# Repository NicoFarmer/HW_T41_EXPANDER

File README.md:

# HW_T41-EXPANDER
Carte électronique Electrobot basée sur un Teensy 4.1

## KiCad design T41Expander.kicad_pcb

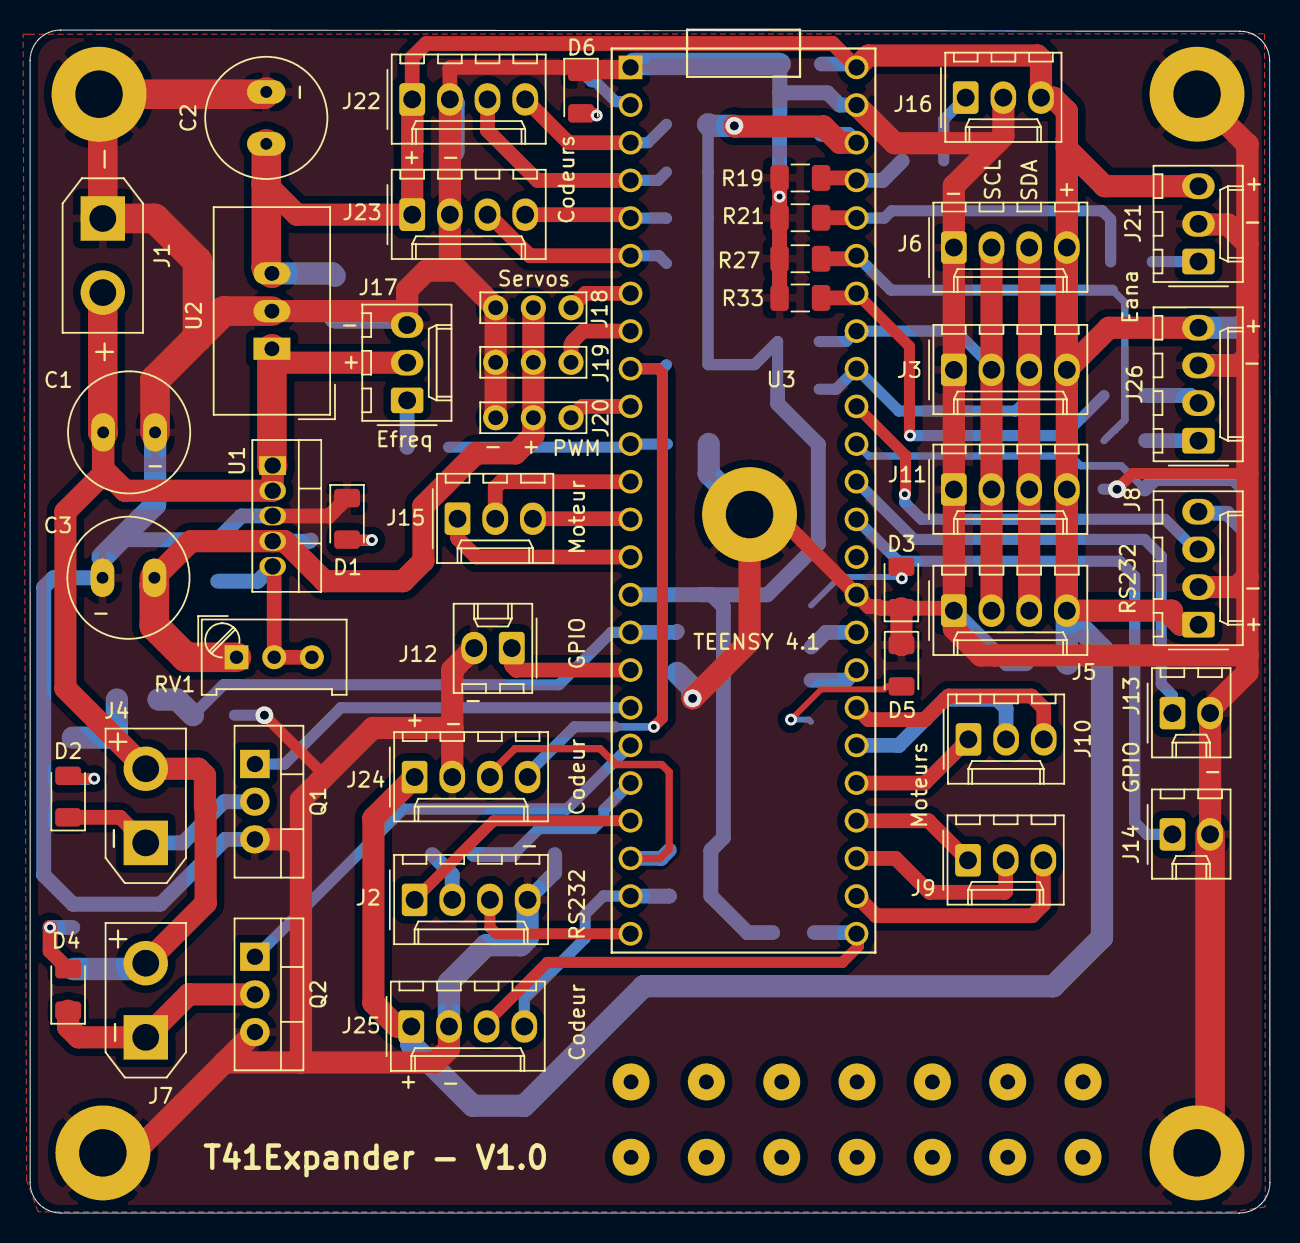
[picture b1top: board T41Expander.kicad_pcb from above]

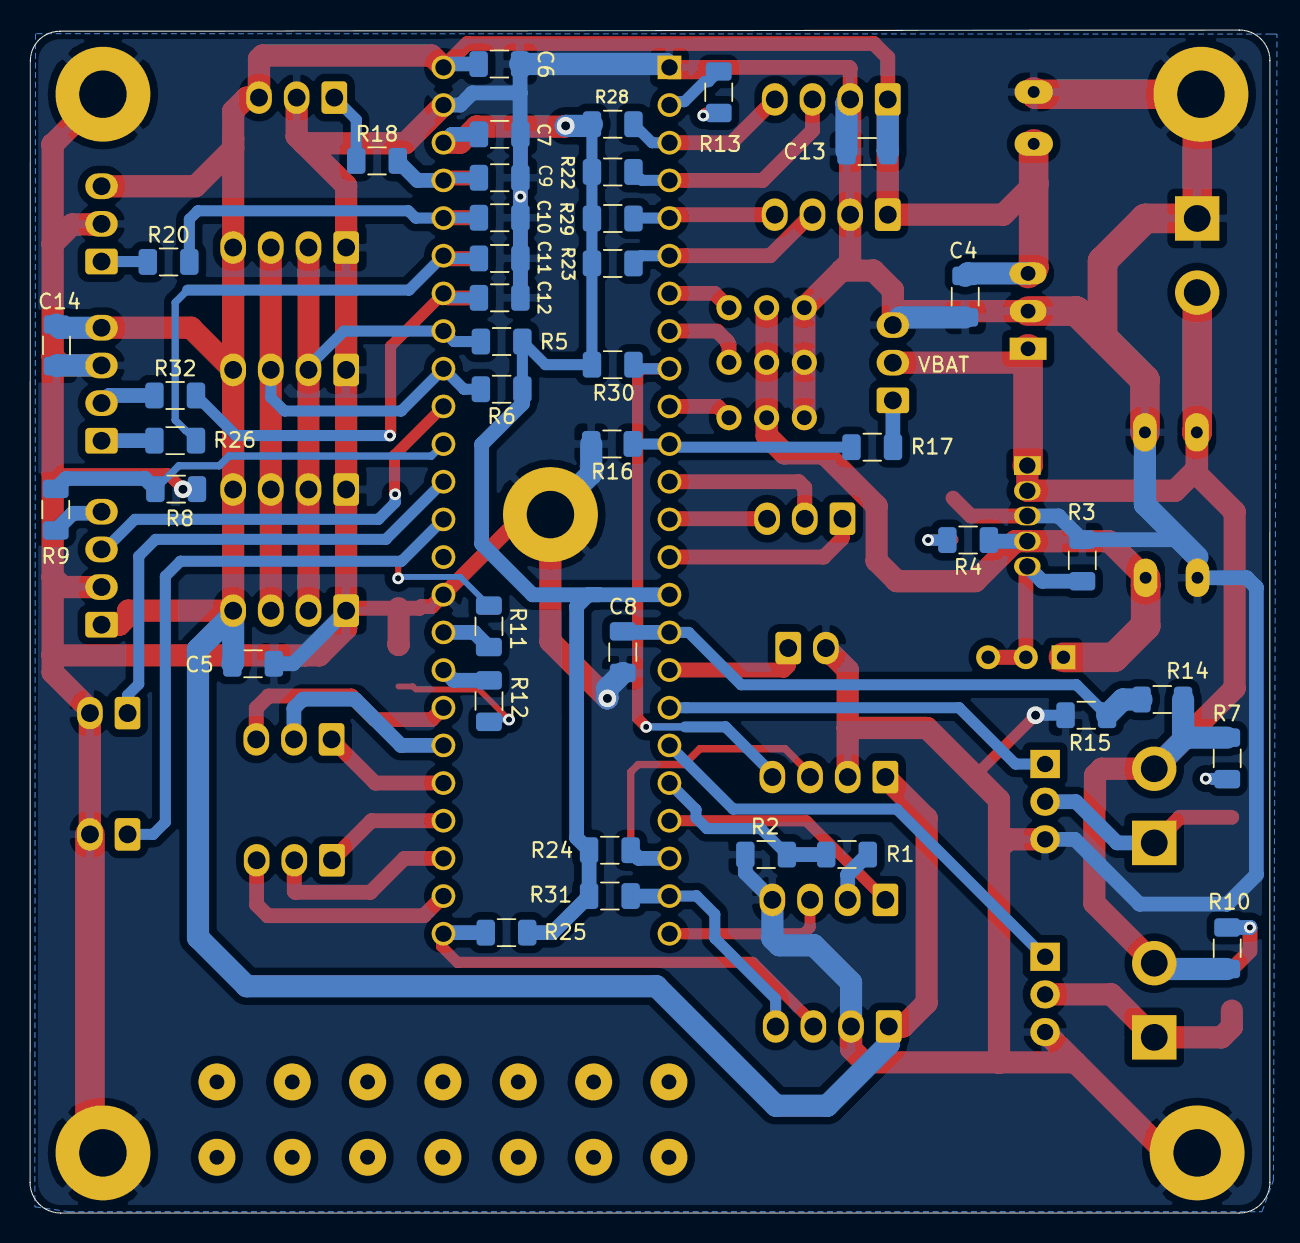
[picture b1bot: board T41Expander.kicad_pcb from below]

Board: 2 copper layers, 83.6 x 79.8 mm, 90 parts (40 on the bottom side), 62 nets.

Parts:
C1, C2, C3: 220u; C_Radial_D8.0mm_H11.5mm_P3.50mm
C4, C6, C7: 100n; C_1206_3216Metric
C5, C13, C14: 47u; C_1206_3216Metric
C8, C9, C10, C11, C12: Value; C_1206_3216Metric
D1, D2, D3, D4, D5, D6: LED; LED_1206_3216Metric
H1, H2, H3, H3#2, H4: MountingHole_Pad; MountingHole_3.2mm_M3_Pad
J1: Conn_XT30; AMASS_XT30UPB-M_1x02_P5.0mm_Vertical
J2, J3, J5, J6, J8, J11, J22, J23, J24, J25, J26: Conn_01x04; Molex_KK-254_AE-6410-04A_1x04_P2.54mm_Vertical
J4, J7: Conn_XT30F; AMASS_XT30UPB-F_1x02_P5.0mm_Vertical
J9, J10, J15: Conn_01x04; Molex_KK-254_AE-6410-03A_1x03_P2.54mm_Vertical
J12, J13, J14: Conn_01x02; Molex_KK-254_AE-6410-02A_1x02_P2.54mm_Vertical
J16, J17, J21: Conn_01x03; Molex_KK-254_AE-6410-03A_1x03_P2.54mm_Vertical
J18, J19, J20: Conn_01x03; Servomotor-3x254
Q1, Q2: BTS117; TO-220-3_Vertical
R1, R9, R22, R23, R24, R25, R28, R29, R30, R31: 10k; R_1206_3216Metric
R2, R8: 18k; R_1206_3216Metric
R3: 220; R_1206_3216Metric
R4, R11, R12, R13: 470; R_1206_3216Metric
R5, R6, R17: 4.7k; R_1206_3216Metric
R7, R10, R14, R15, R18, R19, R20, R21, R26, R27, R32, R33: R; R_1206_3216Metric
R16: 1.8k; R_1206_3216Metric
RV1: 2k; Potentiometer_Trimmer_Bourns_PV36W
U1: MIC29502WT; TO-220-5_Vertical
U2: TSR_2-2450; Converter_DCDC_TRACO_TSR-2_THT
U3: Teensy4.1; Teensy41_no_internal_pins

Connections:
+3V3: C7.1, R5.1, R6.1, R22.1, R23.1, R24.1, R25.1, R28.1, R29.1, R30.1, R31.1, U3.15, U3.46
+5V: C2.1, C4.1, C5.1, C6.1, C13.1, C14.2, J3.4, J5.4, J6.4, J8.1, J11.4, J16.3, J21.3, J22.1, J23.1, J24.1, J25.1, J26.4, U2.3, U3.48
/+Vservo: C3.1, J18.2, J19.2, J20.2, R4.1, RV1.1, U1.4
/CODER_1_A: J22.4, R28.2, U3.3
/CODER_1_B: J22.3, R22.2, U3.4
/CODER_2_A: J23.4, R29.2, U3.5
/CODER_2_B: J23.3, R23.2, U3.6
/CODER_3_A: J24.4, R30.2, U3.9
/CODER_3_B: J24.3, R24.2, U3.22
/CODER_4_A: J25.4, R31.2, U3.23
/CODER_4_B: J25.3, R25.2, U3.25
/Eana1: J16.1, R18.1
/Eana1f: C9.2, R18.2, R19.1, U3.45
/Eana2: J21.1, R20.1
/Eana2f: C10.2, R20.2, R21.1, U3.44
/Eana3: J26.1, R26.1
/Eana3f: C11.2, R26.2, R27.1, U3.43
/Eana4: J26.2, R32.1
/Eana4f: C12.2, R32.2, R33.1, U3.42
/Eana_Vbat: C8.2, R14.2, R15.1, U3.16
/Efreq: J17.1, R17.1
/Efreqf: R16.2, R17.2, U3.11
/GPIO1: J12.1, U3.17
/GPIO2: J13.1, U3.37
/GPIO3: J14.1, U3.36
/I2C_SCL: J3.2, J5.2, J6.2, J11.2, R5.2, U3.41
/I2C_SDA: J3.3, J5.3, J6.3, J11.3, R6.2, U3.40
/LED1: R11.1, U3.33
/LED2: R12.1, U3.32
/LED3: R13.1, U3.2
/MOSFET_1: Q1.1, U3.18
/MOSFET_2: Q2.1, U3.19
/Mot1_PWM: J9.1, U3.28
/Mot1_Sens1: J9.3, U3.26
/Mot1_Sens2: J9.2, U3.27
/Mot2_PWM: J10.1, U3.29
/Mot2_Sens1: J10.3, U3.31
/Mot2_Sens2: J10.2, U3.30
/Mot3_PWM: J15.1, U3.14
/Mot3_Sens1: J15.3, U3.13
/Mot3_Sens2: J15.2, U3.12
/RS232_1_GPIO: J2.3, U3.24
/RS232_1_RX: J2.2, R1.2
/RS232_1_TX: J2.1, U3.21
/RS232_2_RX: J8.4, R9.1
/RS232_2_TX: J8.3, U3.39
/SPWM1: J18.1, U3.7
/SPWM2: J19.1, U3.8
/SPWM3: J20.1, U3.10
/VBAT: C1.1, J1.2, J4.2, J7.2, J17.2, R7.2, R10.2, R14.1, U1.1, U1.2, U2.1
GND: C1.2, C2.2, C3.2, C4.2, C5.2, C6.2, C7.2, C8.1, C9.1, C10.1, C11.1, C12.1, C13.2, C14.1, D1.1, D3.1, D5.1, D6.1, H1.1, H2.1, H3.1, H3#2.1, H4.1, J1.1, J2.4, J3.1, J5.1, J6.1, J8.2, J11.1, J12.2, J13.2, J14.2, J16.2, J17.3, J18.3, J19.3, J20.3, J21.2, J22.2, J23.2, J24.2, J25.2, J26.3, Q1.3, Q2.3, R2.1, R3.2, R8.1, R15.2, R16.1, R19.2, R21.2, R27.2, R33.2, U1.3, U2.2, U3.1, U3.34, U3.47
unnamed: D1.2, R4.2
unnamed: D2.1, J4.1, Q1.2
unnamed: D2.2, R7.1
unnamed: D3.2, R11.2
unnamed: D4.1, J7.1, Q2.2
unnamed: D4.2, R10.1
unnamed: D5.2, R12.2
unnamed: D6.2, R13.2
unnamed: R1.1, R2.2, U3.20
unnamed: R3.1, RV1.2, RV1.3, U1.5
unnamed: R8.2, R9.2, U3.38

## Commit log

2022-02-01 Ajout du sous-module KICAD_LIB
2022-02-01 Ajout du fichier README.md
2022-02-01 Version initiale du projet T41Expander (schéma-routage)
2022-02-01 T41Expander V1.0 envoyé en fabrication
